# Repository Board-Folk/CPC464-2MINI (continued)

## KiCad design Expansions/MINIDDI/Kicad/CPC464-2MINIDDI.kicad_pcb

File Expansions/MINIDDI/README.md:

# MINIDDI

3.5" Disk and Gotek Interface using the 765 disk controller and Epson SED.

# Main points 

* Based on the DDI-1 with modifications for the Epson SED (as found in the 6128).
* This works with standard 3.5" PC Drives, and Goteks having borrowed slight changes from the PPC640.
* Adapter in the Extras folder for use with 3" drives.
* This hasn't really changed since the first release since it works so well. Might need a tidy up.
* More information to follow

# BOM

iBOM can be found in BOM folder.

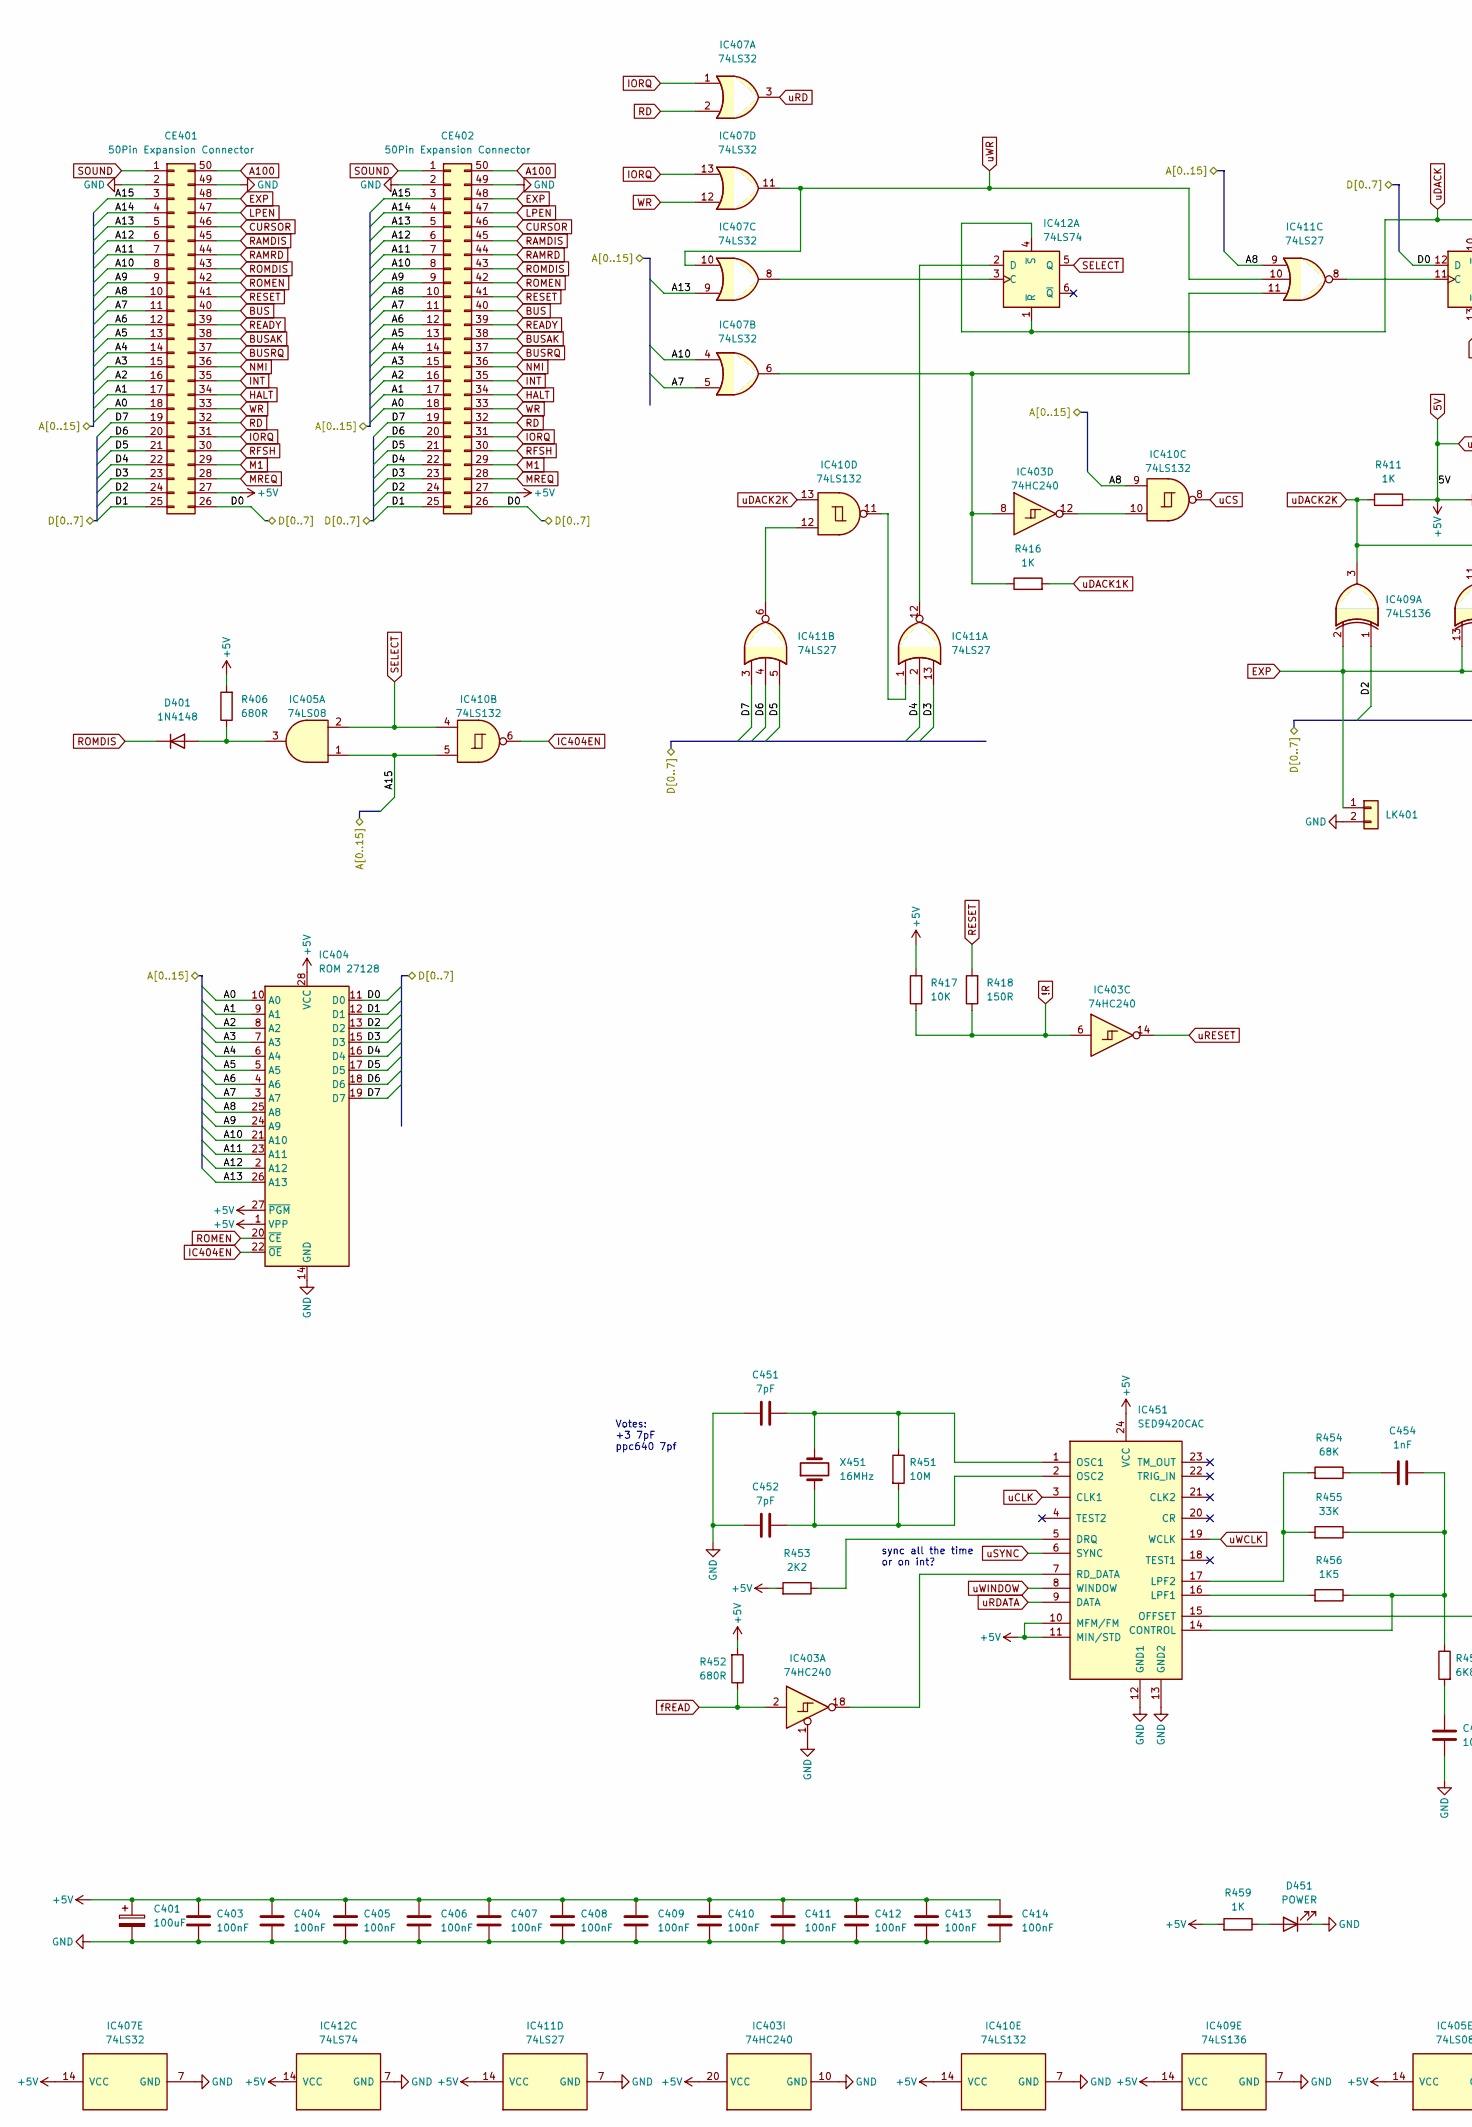
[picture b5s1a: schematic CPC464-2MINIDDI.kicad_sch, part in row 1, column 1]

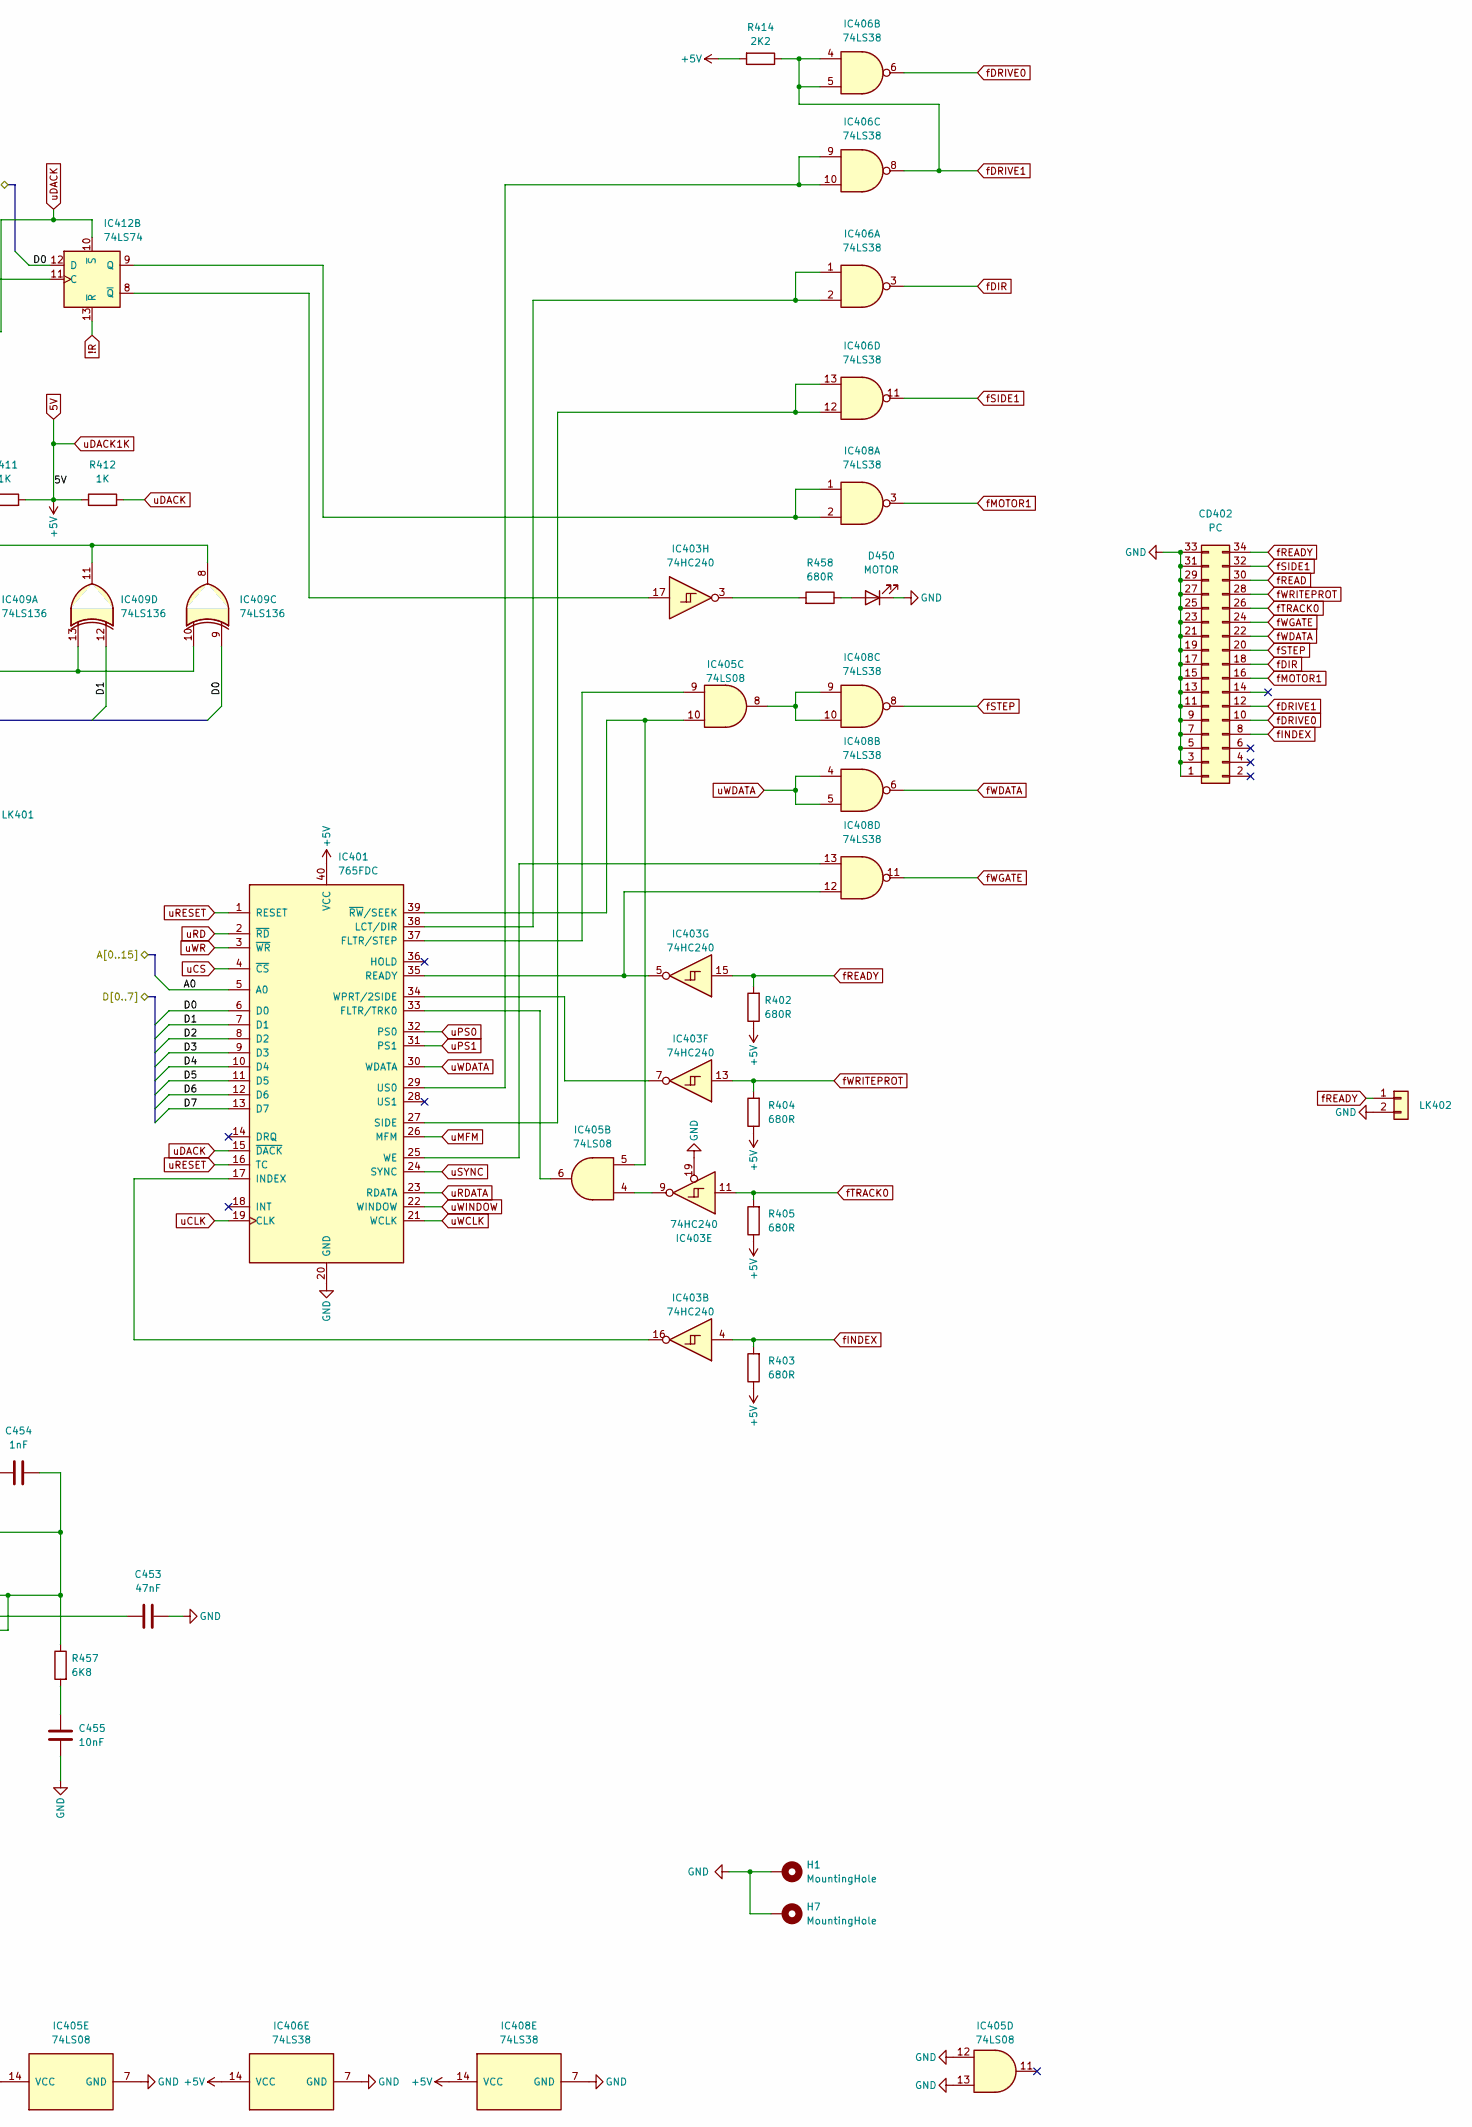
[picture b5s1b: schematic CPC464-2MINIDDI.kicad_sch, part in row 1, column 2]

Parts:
C401: 100uF; CP_Radial_D6.3mm_P2.50mm
C403, C404, C405, C406, C407, C408, C409, C410, C411, C412, C413, C414: 100nF; C_0805_2012Metric
C451, C452: 7pF; C_0805_2012Metric; LCSC C1834
C453: 47nF; C_0805_2012Metric; LCSC C1834
C454: 1nF; C_0805_2012Metric; LCSC C1834
C455: 10nF; C_0805_2012Metric; LCSC C1834
CD402: PC; IDC-Header_2x17_P2.54mm_Vertical
CE401, CE402: 50Pin Expansion Connector; EXPANSION_IDC_ANONYMISED
D401: 1N4148; D_SOD-123
D450: MOTOR; LED_1206_3216Metric
D451: POWER; LED_1206_3216Metric
H1, H7: MountingHole; MountingHole_2.7mm_M2.5_ISO14580_Pad
IC401: 765FDC; DIP-40_W15.24mm
IC403: 74HC240; SOIC-20W_7.5x12.8mm_P1.27mm
IC404: ROM 27128; DIP-28_W15.24mm
IC405: 74LS08; SOIC-14_3.9x8.7mm_P1.27mm
IC406, IC408: 74LS38; SOIC-14_3.9x8.7mm_P1.27mm
IC407: 74LS32; SOIC-14_3.9x8.7mm_P1.27mm
IC409: 74LS136; SOIC-14_3.9x8.7mm_P1.27mm
IC410: 74LS132; SOIC-14_3.9x8.7mm_P1.27mm
IC411: 74LS27; SOIC-14_3.9x8.7mm_P1.27mm
IC412: 74LS74; SOIC-14_3.9x8.7mm_P1.27mm
IC451: SED9420CAC; DIP-24_W15.24mm
LK401: LK401; PinHeader_1x02_P2.54mm_Vertical
LK402: LK402; PinHeader_1x02_P2.54mm_Vertical
R402, R403, R404, R405, R406, R452, R458: 680R; R_0805_2012Metric
R411, R412, R416, R459: 1K; R_0805_2012Metric
R414, R453: 2K2; R_0805_2012Metric
R417: 10K; R_0805_2012Metric
R418: 150R; R_0805_2012Metric
R451: 10M; R_0805_2012Metric; LCSC C309665
R454: 68K; R_0805_2012Metric
R455: 33K; R_0805_2012Metric
R456: 1K5; R_0805_2012Metric
R457: 6K8; R_0805_2012Metric
X451: 16MHz; Crystal_HC49-U_Vertical

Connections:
5V: C401.1, C403.1, C404.1, C405.1, C406.1, C407.1, C408.1, C409.1, C410.1, C411.1, C412.1, C413.1, C414.1, CE401.27, CE402.27, IC401.40 (VCC), IC403.20 (VCC), IC404.1 (VPP), IC404.27 (~PGM), IC404.28 (VCC), IC405.14 (VCC), IC406.14 (VCC), IC407.14 (VCC), IC408.14 (VCC), IC409.14 (VCC), IC410.14 (VCC), IC411.14 (VCC), IC412.14 (VCC), IC451.10 (MFM/FM), IC451.11 (MIN/STD), IC451.24 (VCC), R402.1, R403.1, R404.1, R405.1, R406.2, R411.2, R412.1, R414.2, R416.2, R417.2, R452.2, R453.2, R459.2
!R: IC403.6, IC412.13 (~R), R417.1, R418.1
/A0: CE401.18, CE402.18, IC401.5 (A0), IC404.10 (A0)
/A1: CE401.17, CE402.17, IC404.9 (A1)
/A2: CE401.16, CE402.16, IC404.8 (A2)
/A3: CE401.15, CE402.15, IC404.7 (A3)
/A4: CE401.14, CE402.14, IC404.6 (A4)
/A5: CE401.13, CE402.13, IC404.5 (A5)
/A6: CE401.12, CE402.12, IC404.4 (A6)
/A7: CE401.11, CE402.11, IC404.3 (A7), IC407.5
/A8: CE401.10, CE402.10, IC404.25 (A8), IC410.9, IC411.9
/A9: CE401.9, CE402.9, IC404.24 (A9)
/A10: CE401.8, CE402.8, IC404.21 (A10), IC407.4
/A11: CE401.7, CE402.7, IC404.23 (A11)
/A12: CE401.6, CE402.6, IC404.2 (A12)
/A13: CE401.5, CE402.5, IC404.26 (A13), IC407.9
/A14: CE401.4, CE402.4
/A15: CE401.3, CE402.3, IC405.1, IC410.5
/D0: CE401.26, CE402.26, IC401.6 (D0), IC404.11 (D0), IC409.9, IC412.12 (D)
/D1: CE401.25, CE402.25, IC401.7 (D1), IC404.12 (D1), IC409.12
/D2: CE401.24, CE402.24, IC401.8 (D2), IC404.13 (D2), IC409.1
/D3: CE401.23, CE402.23, IC401.9 (D3), IC404.15 (D3), IC411.13
/D4: CE401.22, CE402.22, IC401.10 (D4), IC404.16 (D4), IC411.2
/D5: CE401.21, CE402.21, IC401.11 (D5), IC404.17 (D5), IC411.5
/D6: CE401.20, CE402.20, IC401.12 (D6), IC404.18 (D6), IC411.4
/D7: CE401.19, CE402.19, IC401.13 (D7), IC404.19 (D7), IC411.3
A100: CE401.50, CE402.50
BUS: CE401.40, CE402.40
BUSAK: CE401.38, CE402.38
BUSRQ: CE401.37, CE402.37
CURSOR: CE401.46, CE402.46
EXP: CE401.48, CE402.48, IC409.2, IC409.10, IC409.13, LK401.1
GND: C401.2, C403.2, C404.2, C405.2, C406.2, C407.2, C408.2, C409.2, C410.2, C411.2, C412.2, C413.2, C414.2, C451.2, C452.2, C453.1, C455.1, CD402.1, CD402.3, CD402.5, CD402.7, CD402.9, CD402.11, CD402.13, CD402.15, CD402.17, CD402.19, CD402.21, CD402.23, CD402.25, CD402.27, CD402.29, CD402.31, CD402.33, CE401.2, CE401.49, CE402.2, CE402.49, D450.1 (K), D451.1 (K), H1.1, H7.1, IC401.20 (GND), IC403.1, IC403.10 (GND), IC403.19, IC404.14 (GND), IC405.7 (GND), IC405.12, IC405.13, IC406.7 (GND), IC407.7 (GND), IC408.7 (GND), IC409.7 (GND), IC410.7 (GND), IC411.7 (GND), IC412.7 (GND), IC451.12 (GND1), IC451.13 (GND2), LK401.2, LK402.2
HALT: CE401.34, CE402.34
IC404EN: IC404.22 (~OE), IC410.6
INT: CE401.35, CE402.35
IORQ: CE401.31, CE402.31, IC407.1, IC407.13
LPEN: CE401.47, CE402.47
M1: CE401.29, CE402.29
MREQ: CE401.28, CE402.28
NMI: CE401.36, CE402.36
unnamed: C451.1, IC451.1 (OSC1), R451.1, X451.2
unnamed: C452.1, IC451.2 (OSC2), R451.2, X451.1
unnamed: C453.2, IC451.15 (OFFSET)
unnamed: C454.1, IC451.14 (CONTROL), R455.1, R456.1, R457.1
unnamed: C454.2, R454.1
unnamed: C455.2, R457.2
unnamed: D401.2 (A), IC405.3, R406.1
unnamed: D450.2 (A), R458.1
unnamed: D451.2 (A), R459.1
unnamed: IC401.17 (INDEX), IC403.16
unnamed: IC401.25 (WE), IC408.13
unnamed: IC401.27 (SIDE), IC406.12, IC406.13
unnamed: IC401.29 (US0), IC406.9, IC406.10
unnamed: IC401.33 (FLTR/TRK0), IC405.6
unnamed: IC401.34 (WPRT/2SIDE), IC403.7
unnamed: IC401.35 (READY), IC403.5, IC408.12
unnamed: IC401.37 (FLTR/STEP), IC405.9
unnamed: IC401.38 (LCT/DIR), IC406.1, IC406.2
unnamed: IC401.39 (~RW/SEEK), IC405.5, IC405.10
unnamed: IC403.3, R458.2
unnamed: IC403.8, IC407.6, IC411.11, R416.1
unnamed: IC403.9, IC405.4
unnamed: IC403.12, IC410.10
unnamed: IC403.17, IC412.8 (~Q)
unnamed: IC403.18, IC451.7 (RD_DATA)
unnamed: IC405.8, IC408.9, IC408.10
unnamed: IC407.8, IC412.3 (C)
unnamed: IC408.1, IC408.2, IC412.9 (Q)
unnamed: IC410.11, IC411.1
unnamed: IC410.12, IC411.6
unnamed: IC411.8, IC412.11 (C)
unnamed: IC411.12, IC412.2 (D)
unnamed: IC451.5 (DRQ), R453.1
unnamed: IC451.16 (LPF1), R456.2
unnamed: IC451.17 (LPF2), R454.2, R455.2
RAMDIS: CE401.45, CE402.45
RAMRD: CE401.44, CE402.44
RD: CE401.32, CE402.32, IC407.2
READY: CE401.39, CE402.39
RESET: CE401.41, CE402.41, R418.2
RFSH: CE401.30, CE402.30
ROMDIS: CE401.43, CE402.43, D401.1 (K)
ROMEN: CE401.42, CE402.42, IC404.20 (~CE)
SELECT: IC405.2, IC410.4, IC412.5 (Q)
SOUND: CE401.1, CE402.1
WR: CE401.33, CE402.33, IC407.12
fDIR: CD402.18, IC406.3
fDRIVE0: CD402.10, IC406.6
fDRIVE1: CD402.12, IC406.4, IC406.5, IC406.8, R414.1
fINDEX: CD402.8, IC403.4, R403.2
fMOTOR1: CD402.16, IC408.3
fREAD: CD402.30, IC403.2, R452.1
fREADY: CD402.34, IC403.15, LK402.1, R402.2
fSIDE1: CD402.32, IC406.11
fSTEP: CD402.20, IC408.8
fTRACK0: CD402.26, IC403.11, R405.2
fWDATA: CD402.22, IC408.6
fWGATE: CD402.24, IC408.11
fWRITEPROT: CD402.28, IC403.13, R404.2
uCLK: IC401.19 (CLK), IC451.3 (CLK1)
uCS: IC401.4 (~CS), IC410.8
uDACK: IC401.15 (~DACK), IC412.1 (~R), IC412.4 (~S), IC412.10 (~S), R412.2
uDACK2K: IC409.3, IC409.8, IC409.11, IC410.13, R411.1
uMFM: IC401.26 (MFM)
uPS0: IC401.32 (PS0)
uPS1: IC401.31 (PS1)
uRD: IC401.2 (~RD), IC407.3
uRDATA: IC401.23 (RDATA), IC451.9 (DATA)
uRESET: IC401.1 (RESET), IC401.16 (TC), IC403.14
uSYNC: IC401.24 (SYNC), IC451.6 (SYNC)
uWCLK: IC401.21 (WCLK), IC451.19 (WCLK)
uWDATA: IC401.30 (WDATA), IC408.4, IC408.5
uWINDOW: IC401.22 (WINDOW), IC451.8 (WINDOW)
uWR: IC401.3 (~WR), IC407.10, IC407.11, IC411.10

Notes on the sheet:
sync all the time or on int?
Votes: +3 7pF ppc640 7pf

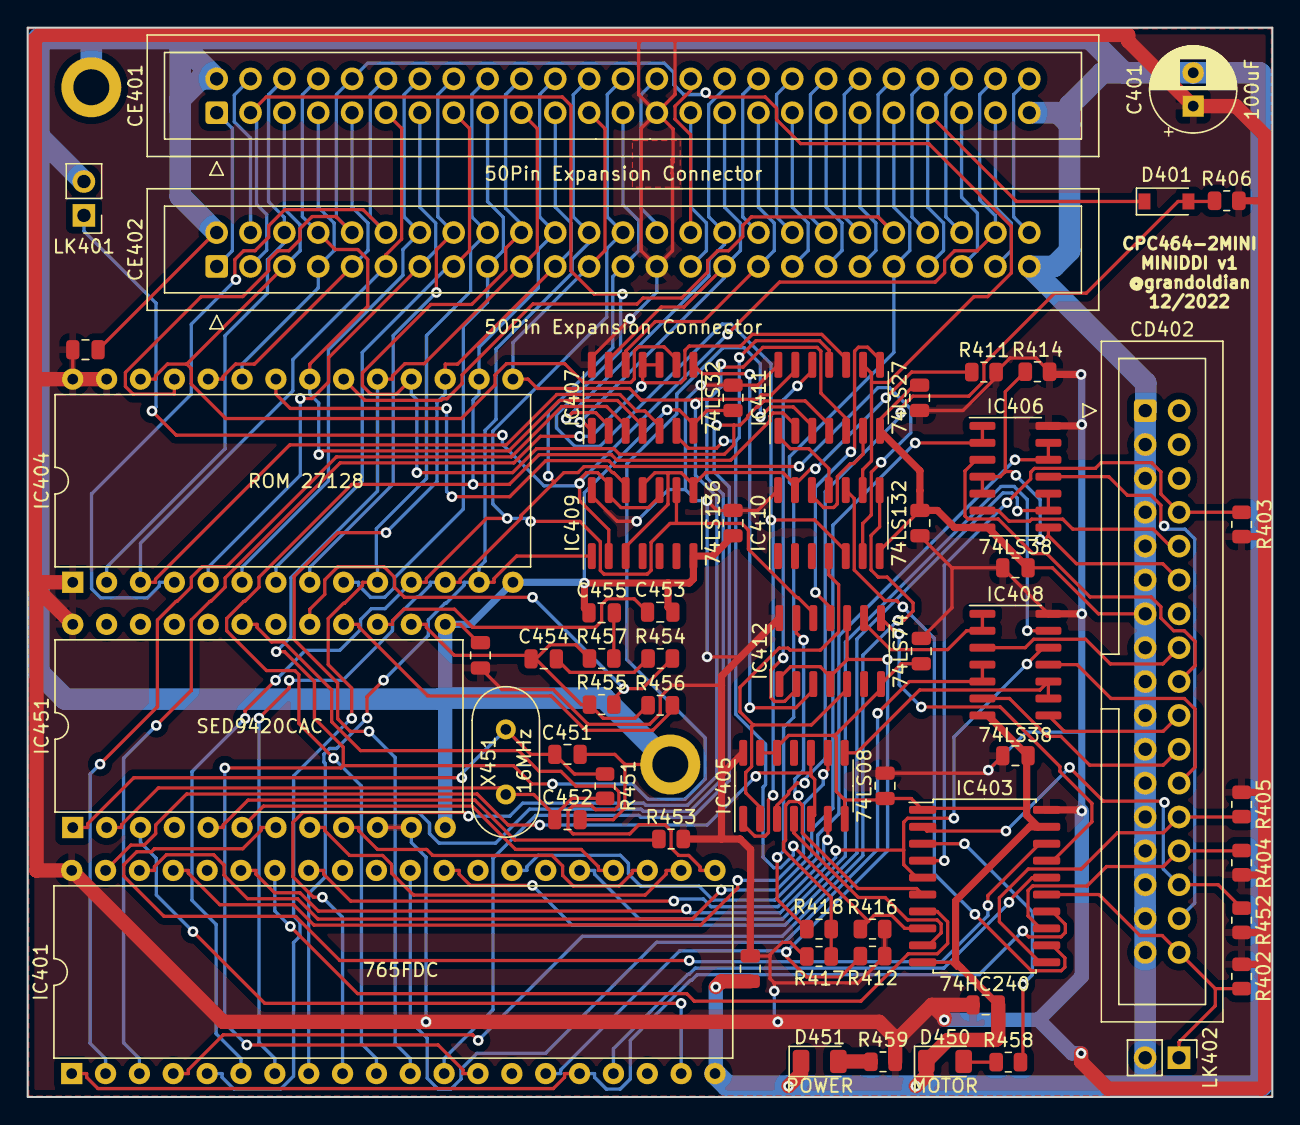
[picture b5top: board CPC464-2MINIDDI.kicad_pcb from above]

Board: 2 copper layers, 93.4 x 80.2 mm, 61 parts (0 on the bottom side), 112 nets.

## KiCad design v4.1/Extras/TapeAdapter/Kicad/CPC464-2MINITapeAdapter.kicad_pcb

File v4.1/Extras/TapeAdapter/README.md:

# CPC464-2MINI Tape Adapter

Tape Adapter for v4 and below revision CPC464-2MINI boards. This does not fit v5, that's to follow.

# Main points 

* This version uses a transistor and slight current limiting to allow you to plug in a standard tape recorder or Tapduino. It mounts on the tape header to the south east of the board instead of an original CPC464 tape player.

# BOM

iBOM can be found in BOM folder.

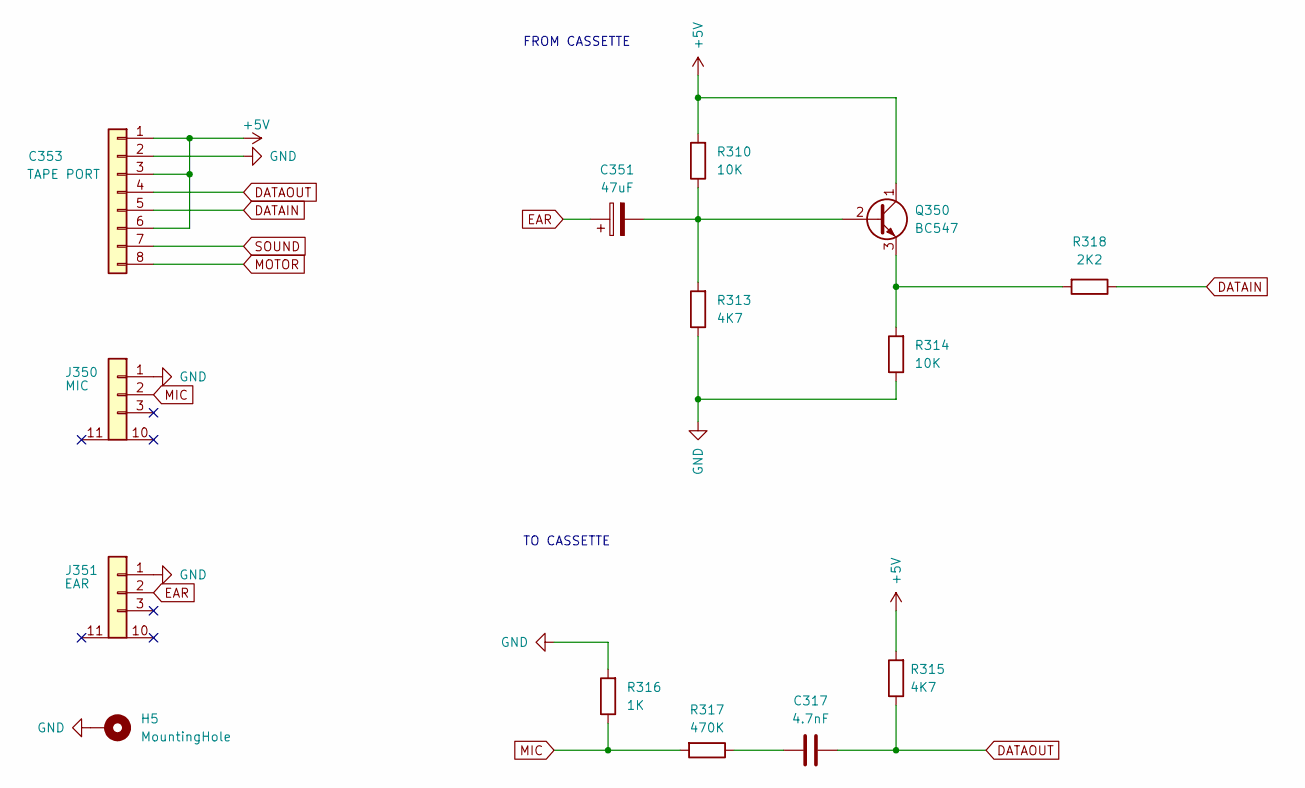
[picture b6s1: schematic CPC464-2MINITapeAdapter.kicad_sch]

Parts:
C317: 4.7nF; C_Disc_D4.3mm_W1.9mm_P5.00mm
C351: 47uF; CP_Radial_D4.0mm_P2.00mm
C353: TAPE PORT; PinHeader_1x08_P2.54mm_Vertical
H5: MountingHole; MountingHole_2.7mm_M2.5_ISO14580_Pad
J350: MIC; STEREO
J351: EAR; STEREO
Q350: BC547; TO92_WIDE
R310, R314: 10K; R_Axial_DIN0204_L3.6mm_D1.6mm_P7.62mm_Horizontal
R313, R315: 4K7; R_Axial_DIN0204_L3.6mm_D1.6mm_P7.62mm_Horizontal
R316: 1K; R_Axial_DIN0204_L3.6mm_D1.6mm_P7.62mm_Horizontal
R317: 470K; R_Axial_DIN0204_L3.6mm_D1.6mm_P7.62mm_Horizontal
R318: 2K2; R_Axial_DIN0204_L3.6mm_D1.6mm_P7.62mm_Horizontal

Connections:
+5V: C353.1, C353.3, C353.6, Q350.1 (C), R310.2, R315.2
DATAIN: C353.5, R318.1
DATAOUT: C317.2, C353.4, R315.1
EAR: C351.1, J351.2
GND: C353.2, H5.1, J350.1, J351.1, R313.1, R314.1, R316.2
MIC: J350.2, R316.1, R317.2
MOTOR: C353.8
unnamed: C317.1, R317.1
unnamed: Q350.3 (E), R314.2, R318.2
unnamed: C351.2, Q350.2 (B), R310.1, R313.2
SOUND: C353.7

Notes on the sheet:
TO CASSETTE
FROM CASSETTE

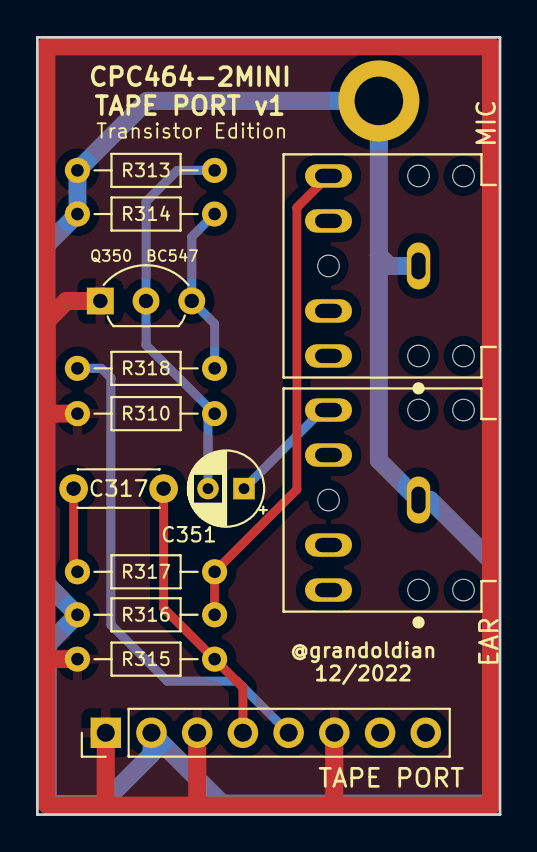
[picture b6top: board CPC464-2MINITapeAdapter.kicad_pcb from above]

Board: 2 copper layers, 25.7 x 43.2 mm, 14 parts (0 on the bottom side), 9 nets.

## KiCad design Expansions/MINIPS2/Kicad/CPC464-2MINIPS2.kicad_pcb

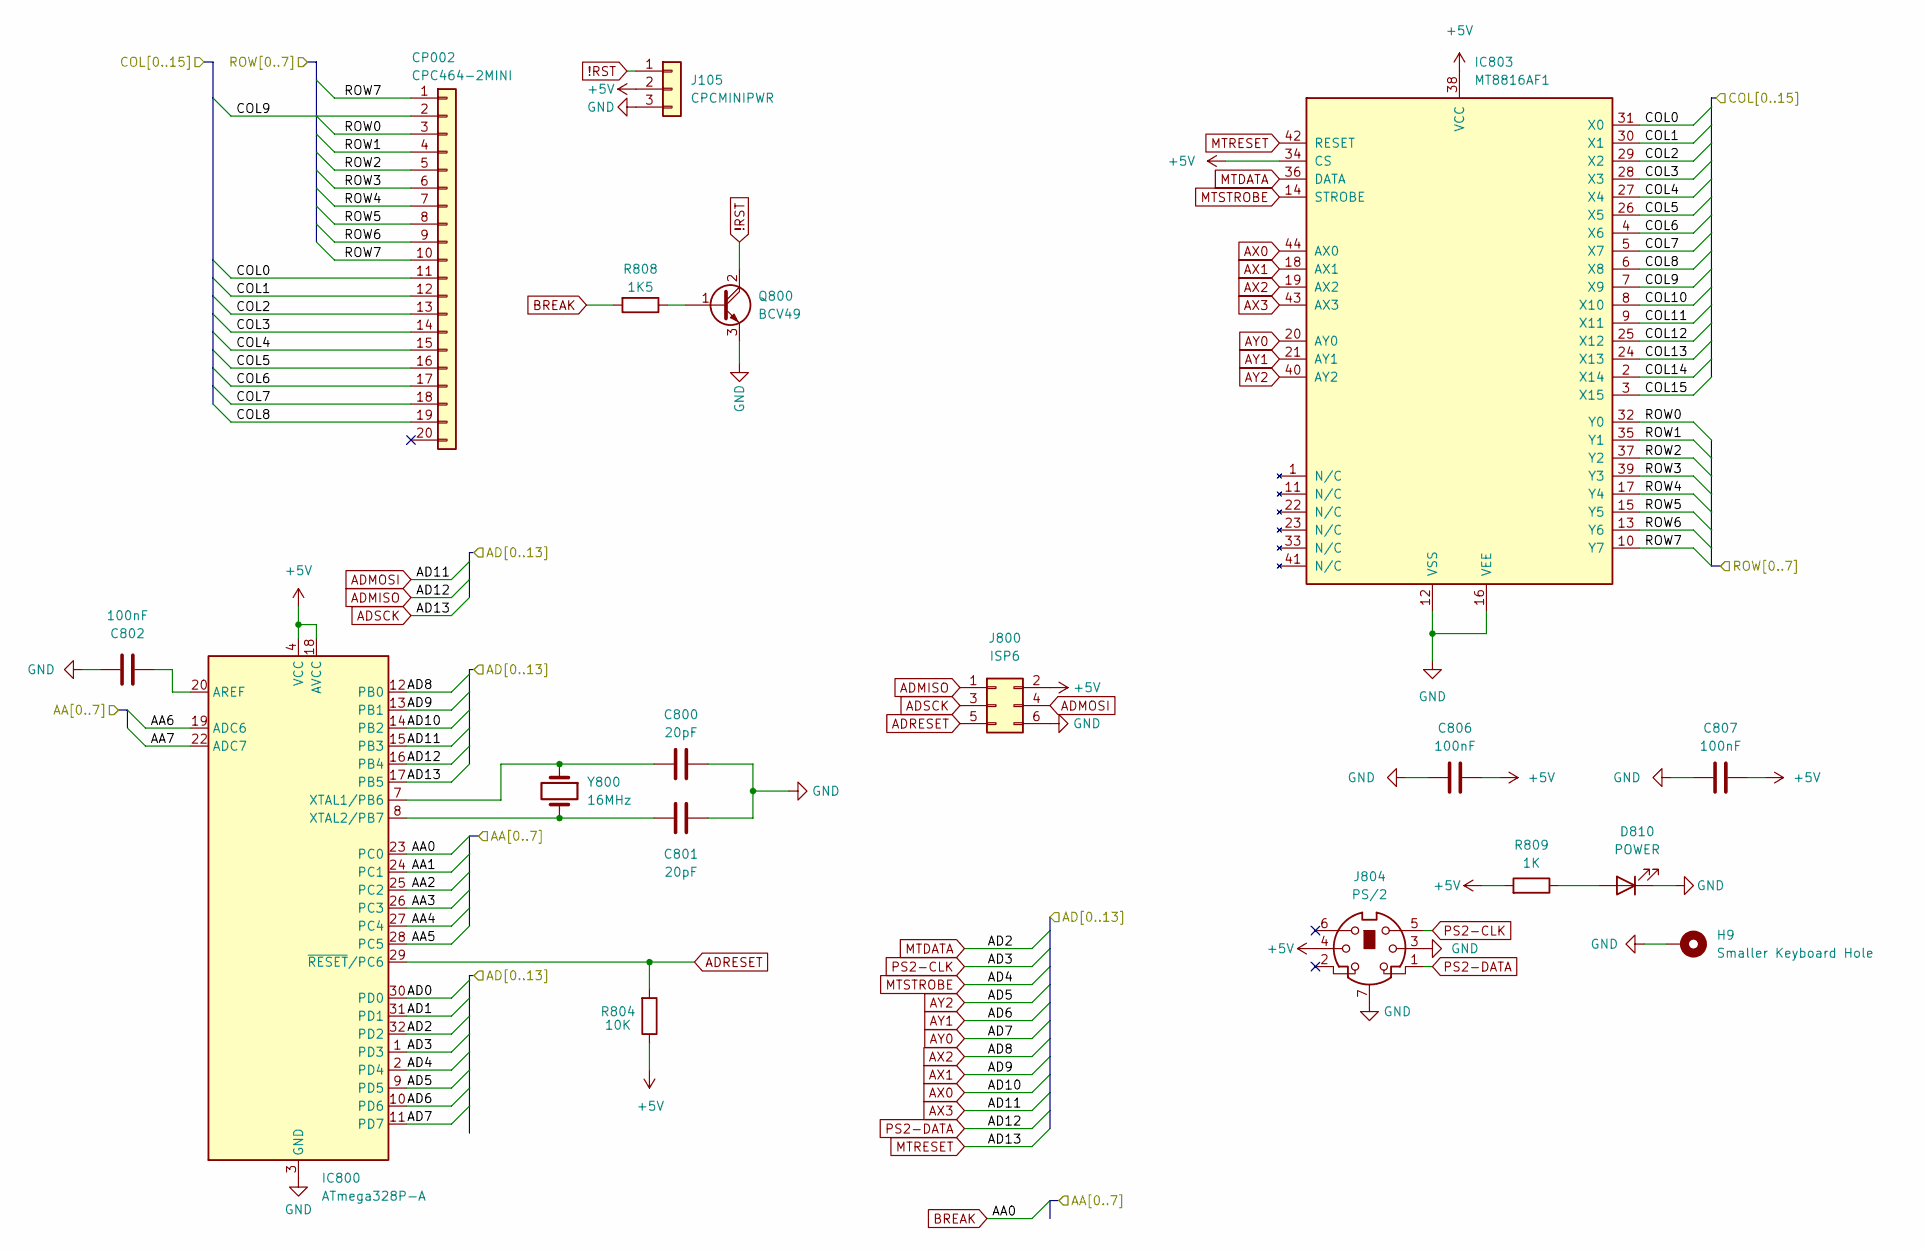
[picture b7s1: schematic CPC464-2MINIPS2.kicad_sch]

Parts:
C800, C801: 20pF; C_0805_2012Metric
C802, C806, C807: 100nF; C_0805_2012Metric
CP002: CPC464-2MINI; PinHeader_1x20_P2.54mm_Vertical
D810: POWER; LED_1206_3216Metric
H9: Smaller Keyboard Hole; MountingHole_2.2mm_M2_DIN965_Pad
IC800: ATmega328P-A; TQFP-32_7x7mm_P0.8mm
IC803: MT8816AF1; TQFP-44_10x10mm_P0.8mm
J105: CPCMINIPWR; PinHeader_1x03_P2.54mm_Vertical
J800: ISP6; PinHeader_2x03_P2.54mm_Vertical
J804: PS/2; Connector_Mini-DIN_Female_6Pin_2rows
Q800: BCV49; SOT-89-3
R804: 10K; R_0805_2012Metric
R808: 1K5; R_0805_2012Metric
R809: 1K; R_0805_2012Metric
Y800: 16MHz; Crystal_HC49-U_Vertical

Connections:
!RST: J105.1, Q800.2 (C)
+5V: C806.2, C807.2, IC800.4 (VCC), IC800.6 (VCC), IC800.18 (AVCC), IC803.34 (CS), IC803.38 (VCC), J105.2, J800.2, J804.4, R804.1, R809.2
/AA1: IC800.24 (PC1)
/AA2: IC800.25 (PC2)
/AA3: IC800.26 (PC3)
/AA4: IC800.27 (PC4)
/AA5: IC800.28 (PC5)
/AA6: IC800.19 (ADC6)
/AA7: IC800.22 (ADC7)
/AD0: IC800.30 (PD0)
/AD1: IC800.31 (PD1)
/COL0: CP002.11, IC803.31 (X0)
/COL1: CP002.12, IC803.30 (X1)
/COL2: CP002.13, IC803.29 (X2)
/COL3: CP002.14, IC803.28 (X3)
/COL4: CP002.15, IC803.27 (X4)
/COL5: CP002.16, IC803.26 (X5)
/COL6: CP002.17, IC803.4 (X6)
/COL7: CP002.18, IC803.5 (X7)
/COL8: CP002.19, IC803.6 (X8)
/COL9: CP002.2, IC803.7 (X9)
/COL10: IC803.8 (X10)
/COL11: IC803.9 (X11)
/COL12: IC803.25 (X12)
/COL13: IC803.24 (X13)
/COL14: IC803.2 (X14)
/COL15: IC803.3 (X15)
/ROW0: CP002.3, IC803.32 (Y0)
/ROW1: CP002.4, IC803.35 (Y1)
/ROW2: CP002.5, IC803.37 (Y2)
/ROW3: CP002.6, IC803.39 (Y3)
/ROW4: CP002.7, IC803.17 (Y4)
/ROW5: CP002.8, IC803.15 (Y5)
/ROW6: CP002.9, IC803.13 (Y6)
/ROW7: CP002.1, CP002.10, IC803.10 (Y7)
ADMOSI: IC800.15 (PB3), IC803.43 (AX3), J800.4
ADRESET: IC800.29 (~RESET/PC6), J800.5, R804.2
ADSCK: IC800.17 (PB5), IC803.42 (RESET), J800.3
AX0: IC800.14 (PB2), IC803.44 (AX0)
AX1: IC800.13 (PB1), IC803.18 (AX1)
AX2: IC800.12 (PB0), IC803.19 (AX2)
AY0: IC800.11 (PD7), IC803.20 (AY0)
AY1: IC800.10 (PD6), IC803.21 (AY1)
AY2: IC800.9 (PD5), IC803.40 (AY2)
BREAK: IC800.23 (PC0), R808.2
GND: C800.2, C801.2, C802.2, C806.1, C807.1, D810.1 (K), H9.1, IC800.3 (GND), IC800.5 (GND), IC800.21 (GND), IC803.12 (VSS), IC803.16 (VEE), J105.3, J800.6, J804.3, J804.7, Q800.3 (E)
MTDATA: IC800.32 (PD2), IC803.36 (DATA)
MTSTROBE: IC800.2 (PD4), IC803.14 (STROBE)
unnamed: C800.1, IC800.7 (XTAL1/PB6), Y800.1
unnamed: C801.1, IC800.8 (XTAL2/PB7), Y800.2
unnamed: C802.1, IC800.20 (AREF)
unnamed: D810.2 (A), R809.1
unnamed: Q800.1 (B), R808.1
PS2-CLK: IC800.1 (PD3), J804.5
PS2-DATA: IC800.16 (PB4), J800.1, J804.1

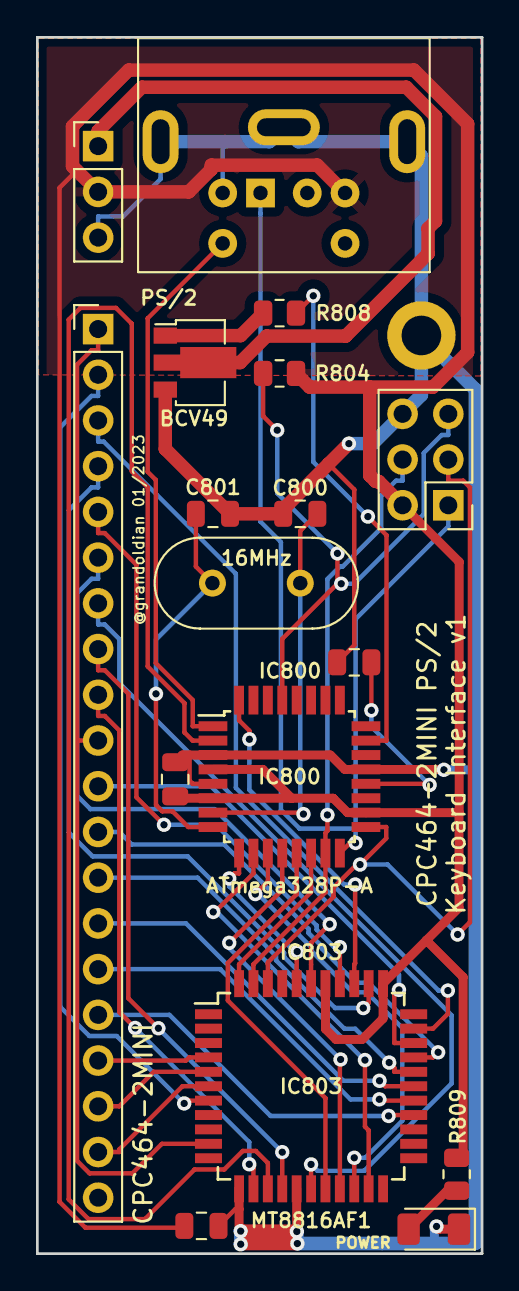
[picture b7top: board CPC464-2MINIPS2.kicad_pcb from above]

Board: 2 copper layers, 24.7 x 67.6 mm, 18 parts (0 on the bottom side), 40 nets.

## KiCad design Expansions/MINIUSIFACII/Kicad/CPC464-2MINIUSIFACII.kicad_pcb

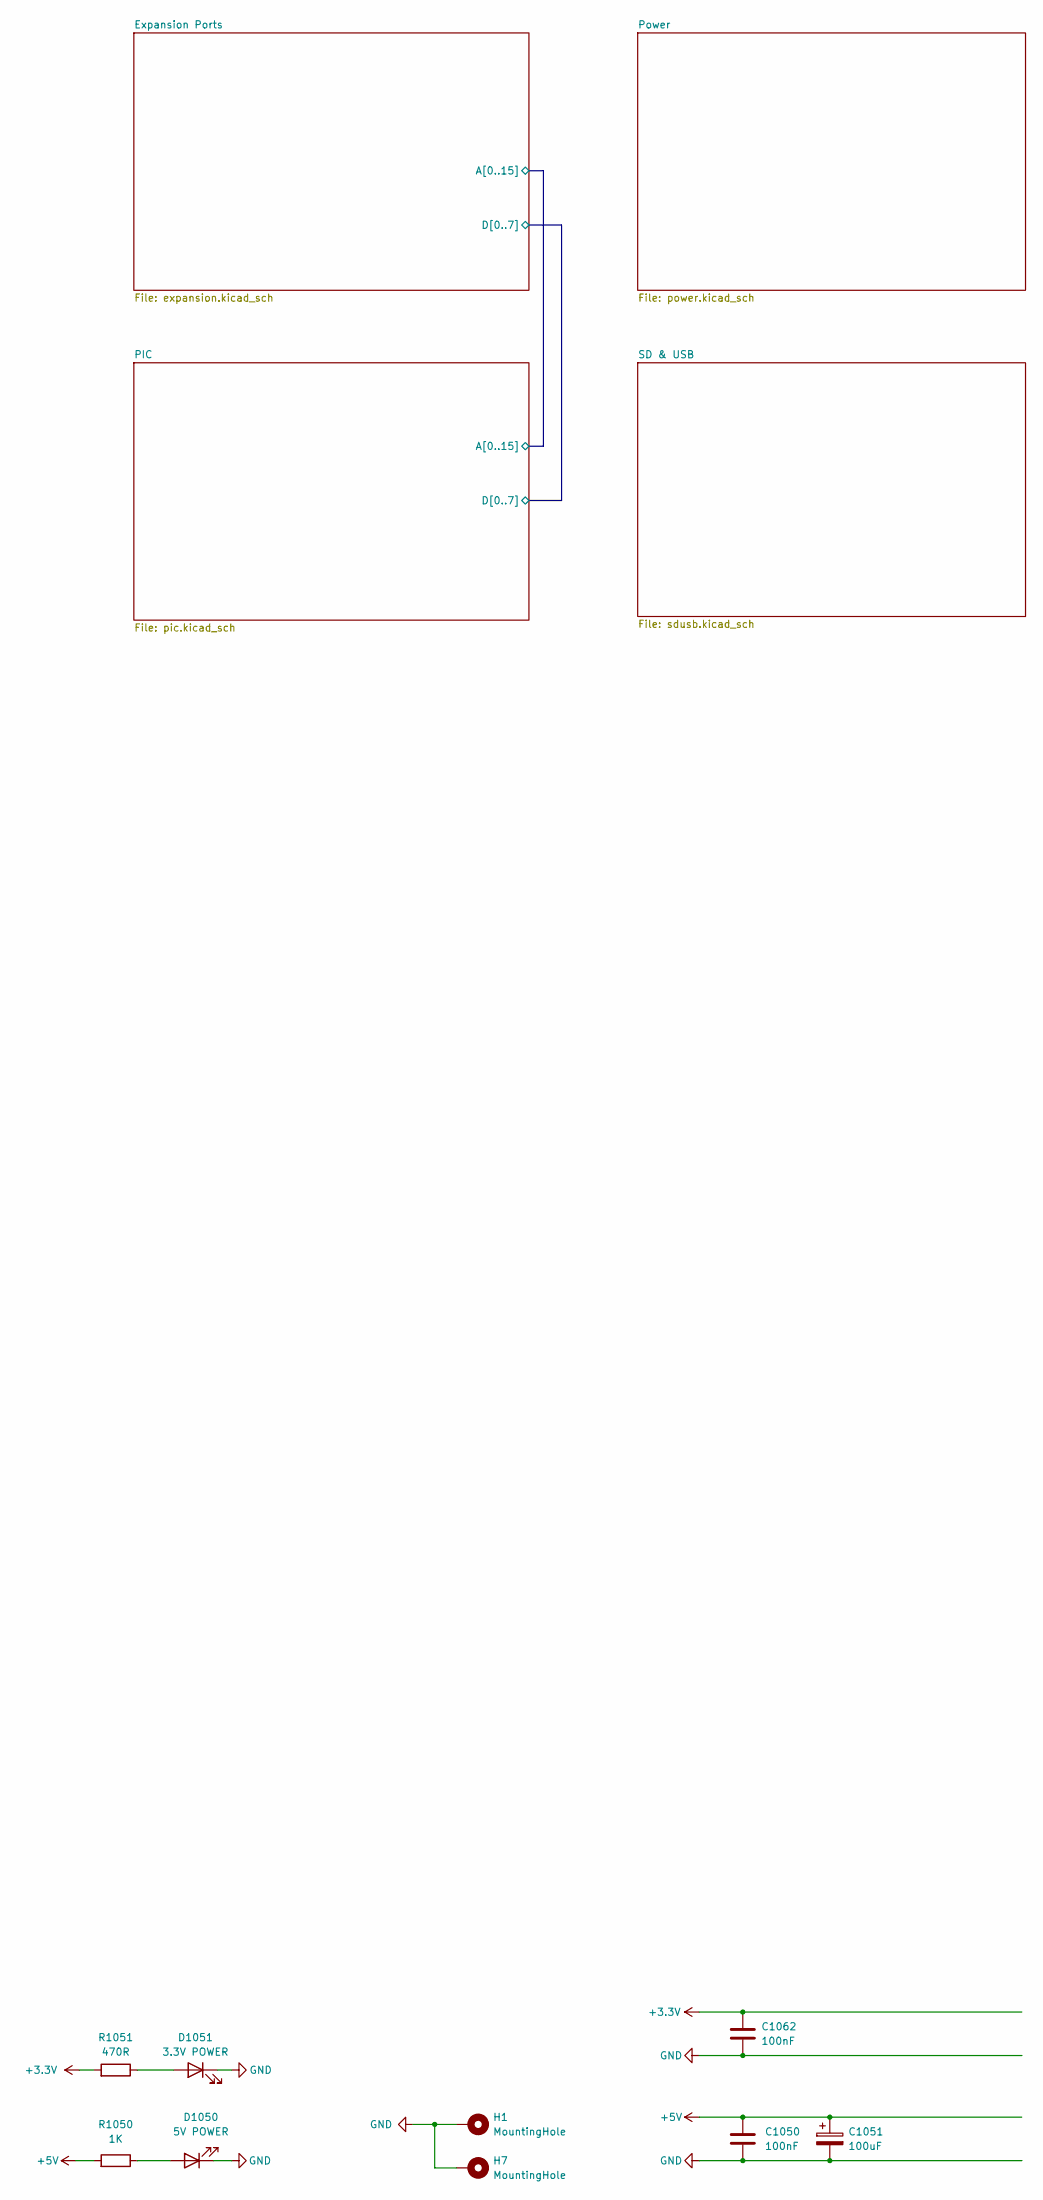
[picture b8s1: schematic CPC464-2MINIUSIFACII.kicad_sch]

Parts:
C1050, C1062: 100nF; C_0805_2012Metric
C1051: 100uF; CP_Radial_D5.0mm_P2.50mm
D1050: 5V POWER; LED_1206_3216Metric
D1051: 3.3V POWER; LED_1206_3216Metric
H1, H7: MountingHole; MountingHole_2.7mm_M2.5_ISO14580_Pad
R1050: 1K; R_0805_2012Metric
R1051: 470R; R_0805_2012Metric

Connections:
+3.3V: C1062.1, R1051.2; also elsewhere on the board
+5V: C1050.1, C1051.1, R1050.2; also elsewhere on the board
GND: C1050.2, C1051.2, C1062.2, D1050.1 (K), D1051.1 (K), H1.1, H7.1; also elsewhere on the board
unnamed: D1050.2 (A), R1050.1
unnamed: D1051.2 (A), R1051.1
